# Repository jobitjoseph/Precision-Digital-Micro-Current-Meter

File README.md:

# Precision-Digital-Micro-Current-Meter

Keeping track of extremely low current levels is often essential when developing or testing low-power devices, especially in the field of embedded systems and battery-operated electronics. This project presents a compact and reliable micro current meter that makes such measurements straightforward and accessible. It is built around an STM32 microcontroller and features an OLED display for real-time readouts. The analog front end is designed to detect small current flows accurately, converting them into voltage levels that the microcontroller can process with high resolution. Whether you're measuring sleep current in a sensor node or characterising a power-efficient circuit, the device offers a clear and immediate view of power consumption trends.

The meter is designed for ease of use on the workbench, with a focus on readability, stability, and portability. The OLED display provides a crisp output that remains visible under most lighting conditions, while the microcontroller handles signal processing and automatic range detection. Calibration routines ensure measurement consistency across various load conditions. With no need for external tools or complex setups, the device offers a plug-and-play experience for engineers, developers, or hobbyists working with ultra-low power electronics. Its practical design makes it a useful tool for anyone seeking to analyse power usage with precision and simplicity.

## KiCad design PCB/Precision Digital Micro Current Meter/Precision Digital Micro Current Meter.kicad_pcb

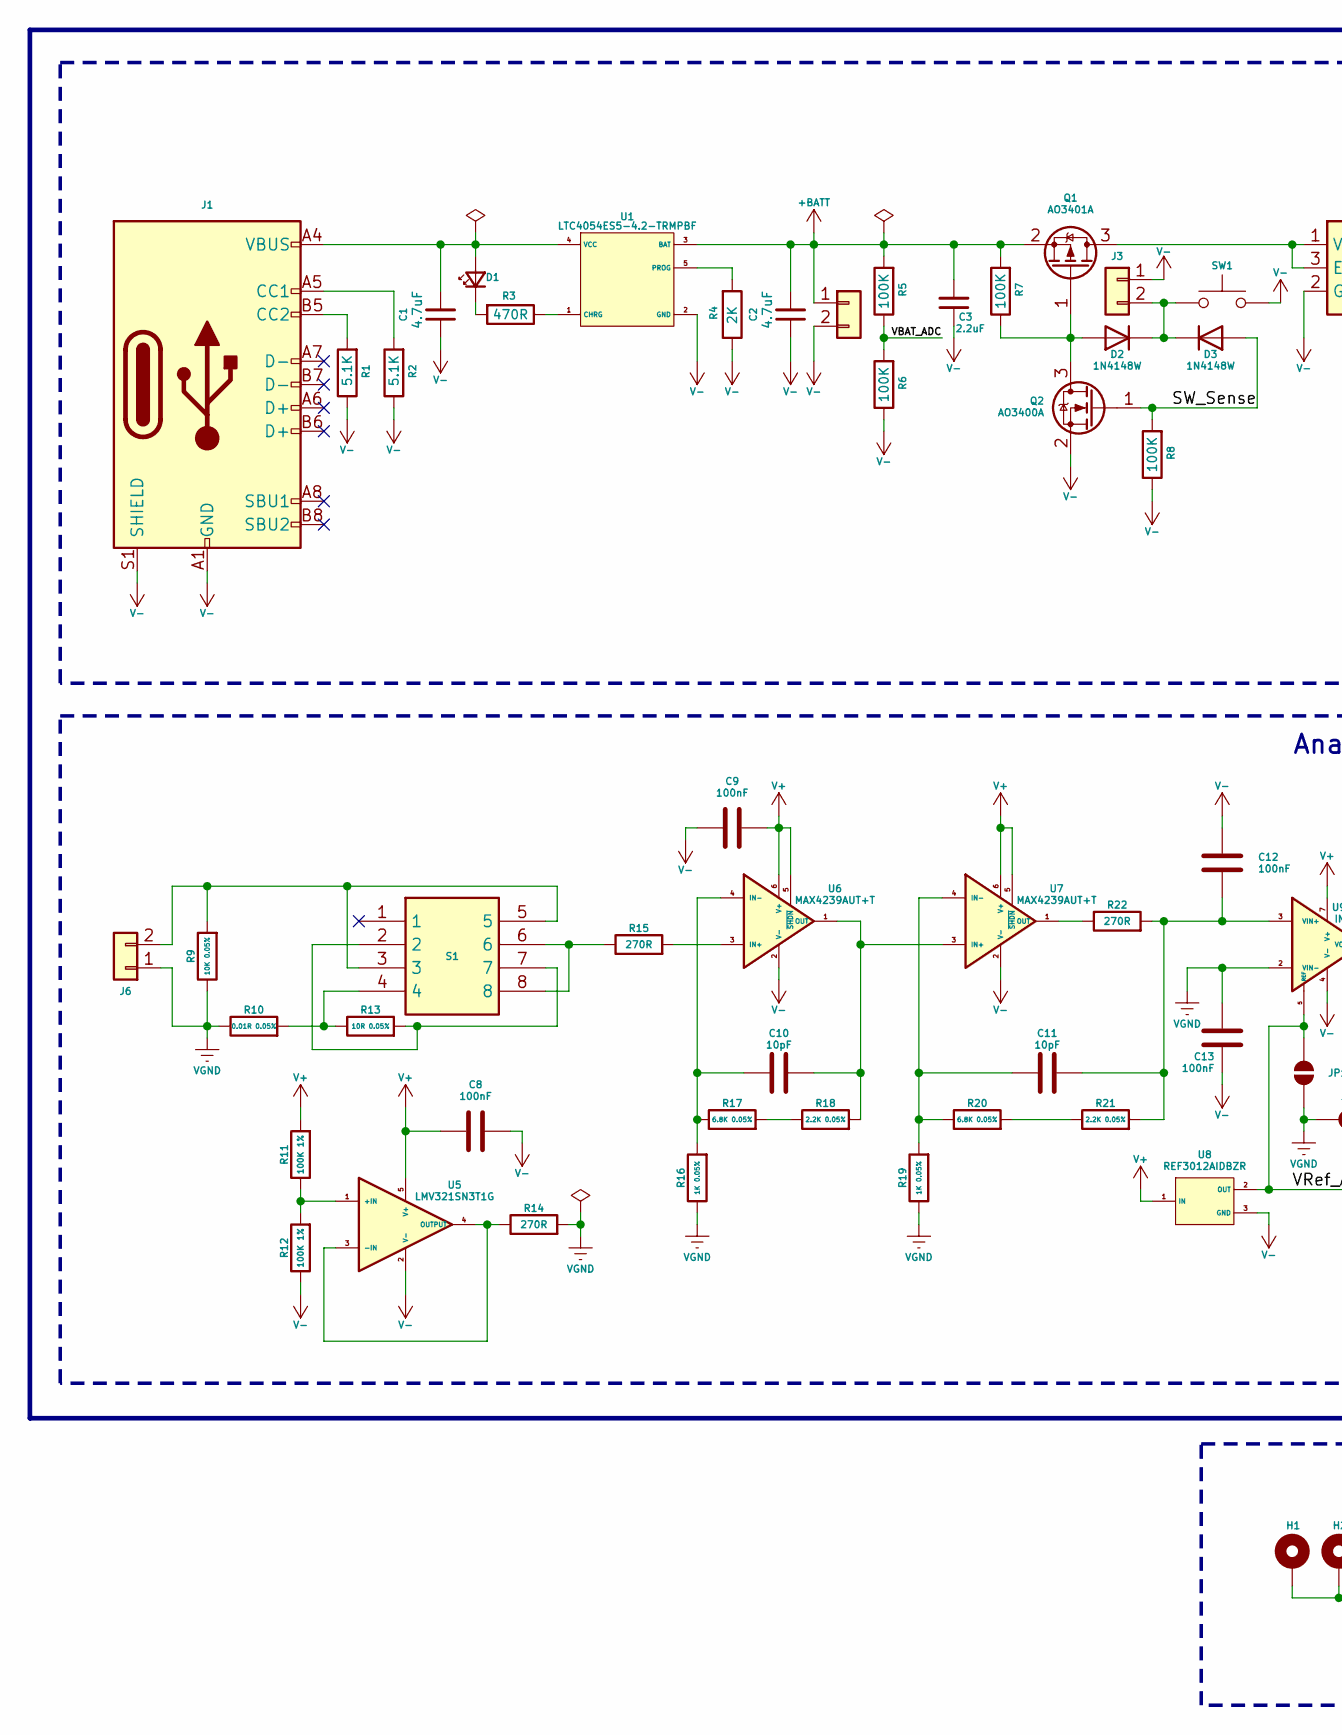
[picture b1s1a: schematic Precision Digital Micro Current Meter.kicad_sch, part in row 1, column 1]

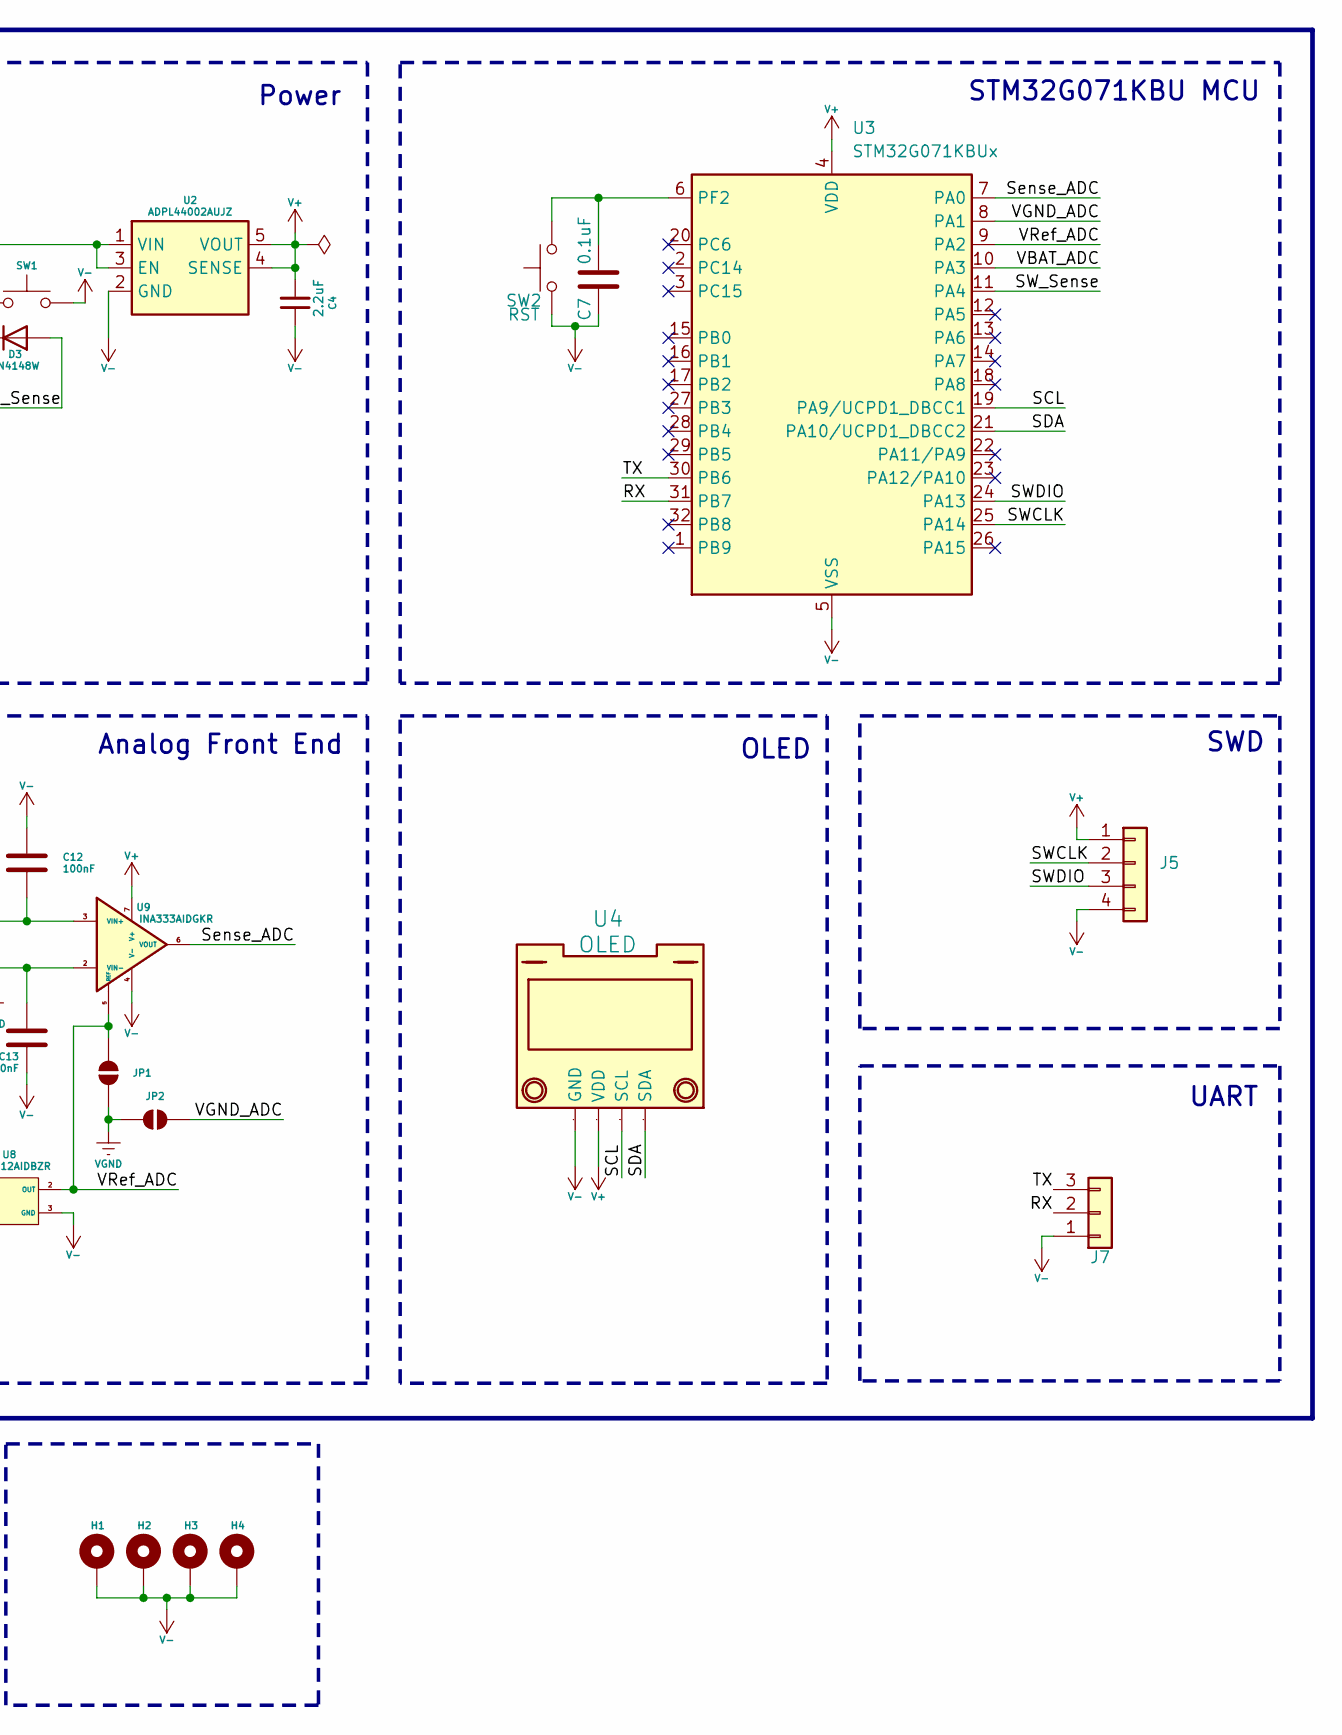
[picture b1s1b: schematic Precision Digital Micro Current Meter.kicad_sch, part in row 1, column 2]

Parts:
C1, C2: 4.7uF; C_0603_1608Metric
C3, C4: 2.2uF; C_0603_1608Metric
C7: 0.1uF; C_0603_1608Metric
C8, C9, C12, C13: 100nF; C_0603_1608Metric
C10, C11: 10pF; C_0603_1608Metric
D1: LED_Small; LED_0603_1608Metric
D2, D3: 1N4148W; D_SOD-123
H1, H2, H3, H4: MountingHole_Pad; MountingHole_2.5mm_Pad
J1: USB_C_Receptacle_USB2.0_16P; USB_C_Receptacle_Palconn_UTC16-G
J2: B2B-PH-SM4-TB(LF)(SN); JST_PH_B2B-PH-K_1x02_P2.00mm_Vertical; DigiKey Part Number 455-1704-ND
J3: Conn_01x02; JST_PH_B2B-PH-K_1x02_P2.00mm_Vertical
J5: Conn_01x04; PinHeader_1x04_P2.54mm_Vertical
J6: Conn_01x02; Banana_Jack_2Pin
J7: Conn_01x03; PinHeader_1x03_P2.54mm_Vertical
JP1, JP2: SolderJumper_2_Open; SolderJumper-2_P1.3mm_Open_TrianglePad1.0x1.5mm
Q1: AO3401A; SOT-23
Q2: AO3400A; SOT-23
R1, R2: 5.1K; R_0603_1608Metric
R3: 470R; R_0603_1608Metric
R4: 2K; R_0603_1608Metric
R5, R6, R7, R8: 100K; R_0603_1608Metric
R9: 10K 0.05%; R_0805_2012Metric
R10: 0.01R 0.05%; R_2512_6332Metric
R11, R12: 100K 1%; R_0603_1608Metric
R13: 10R 0.05%; R_0805_2012Metric
R14, R15, R22: 270R; R_0603_1608Metric
R16, R19: 1K 0.05%; R_0603_1608Metric
R17, R20: 6.8K 0.05%; R_0603_1608Metric
R18, R21: 2.2K 0.05%; R_0603_1608Metric
S1: L203011MS02Q; L203111MS02Q; Mouser Part Number 611-L203011MS02Q
SW1: SW_Push; SW_PUSH_6mm
SW2: RST; Tactile 3x4x2mm TS-A010
U1: LTC4054ES5-4.2-TRMPBF; S_5_ADI
U2: ADPL44002AUJZ; SOT95P280X100-5N; Manufacturer_Part_Number ADPL44002AUJZ2.5-R7
U3: STM32G071KBUx; QFN-32-1EP_5x5mm_P0.5mm_EP3.45x3.45mm
U4: OLED; MODULE_DM-OLED096-636
U5: LMV321SN3T1G; SOT95P275X110-5N; Mouser Part Number 863-LMV321SN3T1G
U6, U7: MAX4239AUT+T; SOT95P280X145-6N; Mouser Part Number 700-MAX4239AUT+T
U8: REF3012AIDBZR; DBZ3
U9: INA333AIDGKR; SOP65P490X110-8N

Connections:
+BATT: C2.2, C3.2, J2.1, Q1.2 (S), R5.2, R7.2, U1.3 (BAT)
/RX: J7.2, U3.31 (PB7); also elsewhere on the board
/SCL: U3.19 (PA9/UCPD1_DBCC1), U4.3 (SCL)
/SDA: U3.21 (PA10/UCPD1_DBCC2), U4.4 (SDA)
/SWCLK: J5.2, U3.25 (PA14)
/SWDIO: J5.3, U3.24 (PA13)
/SW_Sense: D3.2 (A), Q2.1 (G), R8.2, U3.11 (PA4)
/Sense_ADC: U3.7 (PA0), U9.6 (VOUT)
/TX: J7.3, U3.30 (PB6); also elsewhere on the board
/VBAT_ADC: R5.1, R6.2, U3.10 (PA3)
/VGND_ADC: JP2.1 (A), U3.8 (PA1)
/VRef_ADC: JP1.2 (B), U3.9 (PA2), U8.2 (OUT), U9.5 (REF)
unnamed: C1.2, D1.2 (A), J1.A4 (VBUS), J1.A9 (VBUS), J1.B4 (VBUS), J1.B9 (VBUS), U1.4 (VCC)
unnamed: D1.1 (K), R3.2
unnamed: D2.2 (A), Q1.1 (G), Q2.3 (D), R7.1
unnamed: D2.1 (K), D3.1 (K), J3.2, SW1.1
unnamed: J1.A5 (CC1), R2.2
unnamed: J1.B5 (CC2), R1.2
unnamed: J6.2, R9.2, S1.3, S1.5
unnamed: Q1.3 (D), U2.1 (VIN), U2.3 (EN)
unnamed: R10.2, R13.1, S1.4
unnamed: R13.2, S1.2, S1.7
unnamed: R15.1, S1.6, S1.8
unnamed: R17.2, R18.1
unnamed: R20.2, R21.1
unnamed: R3.1, U1.1 (CHRG)
unnamed: R4.2, U1.5 (PROG)
unnamed: C7.2, SW2.2, U3.6 (PF2)
unnamed: R11.1, R12.2, U5.1 (+IN)
unnamed: R14.1, U5.3 (-IN), U5.4 (OUTPUT)
unnamed: R15.2, U6.3 (IN+)
unnamed: C10.1, R16.2, R17.1, U6.4 (IN-)
unnamed: C10.2, R18.2, U6.1 (OUT), U7.3 (IN+)
unnamed: C11.1, R19.2, R20.1, U7.4 (IN-)
unnamed: R22.1, U7.1 (OUT)
unnamed: C11.2, C12.1, R21.2, R22.2, U9.3 (VIN+)
V+: C4.2, C8.1, C9.2, J5.1, R11.2, U2.4 (SENSE), U2.5 (VOUT), U3.4 (VDD), U4.2 (VDD), U5.5 (V+), U6.5 (~SHDN), U6.6 (V+), U7.5 (~SHDN), U7.6 (V+), U8.1 (IN), U9.7 (V+)
V-: C1.1, C2.1, C3.1, C4.1, C7.1, C8.2, C9.1, C12.2, C13.1, H1.1, H2.1, H3.1, H4.1, J1.A1 (GND), J1.A12 (GND), J1.B1 (GND), J1.B12 (GND), J1.S1 (SHIELD), J2.2, J3.1, J5.4, J7.1, Q2.2 (S), R1.1, R2.1, R4.1, R6.1, R8.1, R12.1, SW1.2, SW2.1, U1.2 (GND), U2.2 (GND), U3.5 (VSS), U3.33 (VSS), U4.1 (GND), U5.2 (V-), U6.2 (V-), U7.2 (V-), U8.3 (GND), U9.4 (V-); also elsewhere on the board
VGND: C13.2, J6.1, JP1.1 (A), JP2.2 (B), R9.1, R10.1, R14.2, R16.1, R19.1, U9.2 (VIN-)

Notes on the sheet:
Power
STM32G071KBU MCU
OLED
UART
SWD
Analog Front End

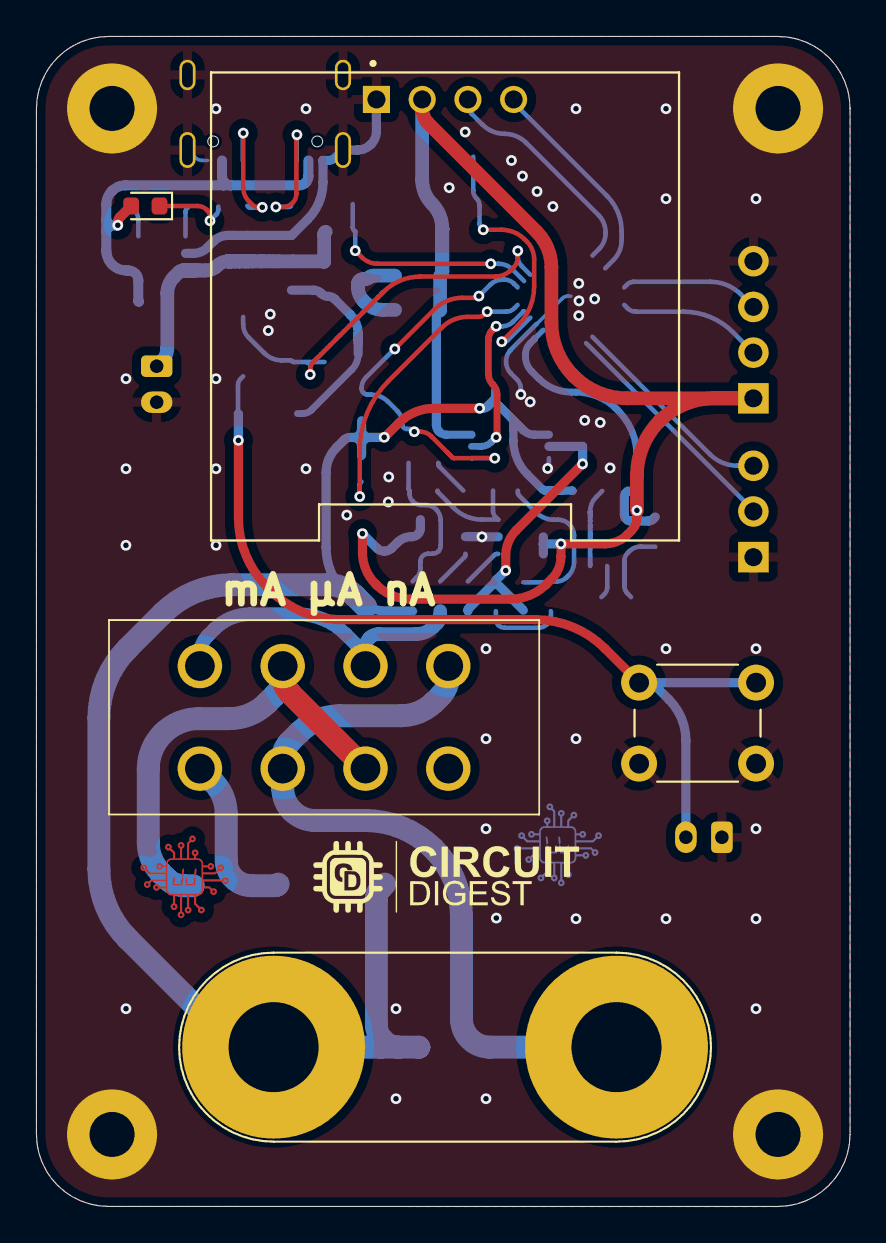
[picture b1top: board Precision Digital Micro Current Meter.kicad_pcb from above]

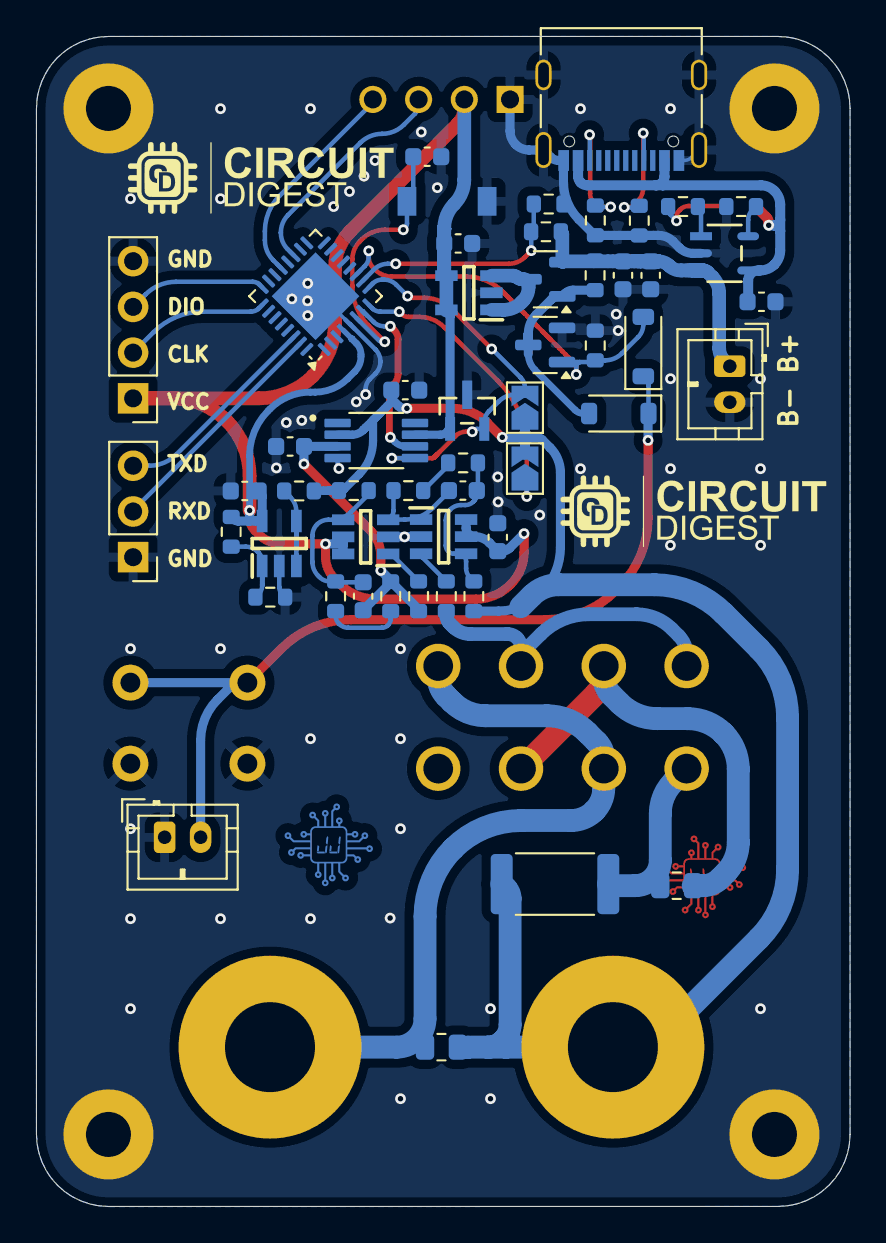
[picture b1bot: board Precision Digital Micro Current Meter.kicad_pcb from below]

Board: 2 copper layers, 45.2 x 65.0 mm, 62 parts (53 on the bottom side), 39 nets.

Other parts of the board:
J4: Conn_01x03; PinHeader_1x03_P2.54mm_Vertical

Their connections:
/RX: J4.2; also elsewhere on the board
/TX: J4.3; also elsewhere on the board
V-: J4.1; also elsewhere on the board

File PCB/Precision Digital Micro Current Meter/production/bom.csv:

Designator,Footprint,Quantity,Value,LCSC Part #
"C1, C2",0603,2,4.7uF,
"C10, C11",0603,2,10pF,
"C12, C13, C8, C9",0603,4,100nF,
"C3, C4",0603,2,2.2uF,
C7,0603,1,0.1uF,
D1,0603,1,LED_Small,
"D2, D3",D_SOD-123,2,1N4148W,
J1,USB_C_Receptacle_Palconn_UTC16-G,1,USB_C_Receptacle_USB2.0_16P,
J2,JST_PH_B2B-PH-K_1x02_P2.00mm_Vertical,1,B2B-PH-SM4-TB(LF)(SN),
J3,JST_PH_B2B-PH-K_1x02_P2.00mm_Vertical,1,Conn_01x02,
J4,PinHeader_1x03_P2.54mm_Vertical,1,Conn_01x03,
J5,PinHeader_1x04_P2.54mm_Vertical,1,Conn_01x04,
J6,Banana_Jack_2Pin,1,Conn_01x02,
"JP1, JP2",SolderJumper-2_P1.3mm_Open_TrianglePad1.0x1.5mm,2,SolderJumper_2_Open,
Q1,SOT-23,1,AO3401A,
Q2,SOT-23,1,AO3400A,
"R1, R2",0603,2,5.1K,
R10,2512,1,0.01R 0.05%,
"R11, R12",0603,2,100K 1%,
R13,0805,1,10R 0.05%,
"R14, R15, R22",0603,3,270R,
"R16, R19",0603,2,1K 0.05%,
"R17, R20",0603,2,6.8K 0.05%,
"R18, R21",0603,2,2.2K 0.05%,
R3,0603,1,470R,
R4,0603,1,2K,
"R5, R6, R7, R8",0603,4,100K,
R9,0805,1,10K 0.05%,
S1,L203111MS02Q,1,L203011MS02Q,
SW1,SW_PUSH_6mm,1,SW_Push,
SW2,Tactile 3x4x2mm TS-A010,1,RST,
U1,S_5_ADI,1,LTC4054ES5-4.2-TRMPBF,
U2,SOT95P280X100-5N,1,ADPL44002AUJZ,
U3,QFN-32-1EP_5x5mm_P0.5mm_EP3.45x3.45mm,1,STM32G071KBUx,
U4,MODULE_DM-OLED096-636,1,OLED,
U5,SOT95P275X110-5N,1,LMV321SN3T1G,
"U6, U7",SOT95P280X145-6N,2,MAX4239AUT+T,
U8,DBZ3,1,REF3012AIDBZR,
U9,SOP65P490X110-8N,1,INA333AIDGKR,

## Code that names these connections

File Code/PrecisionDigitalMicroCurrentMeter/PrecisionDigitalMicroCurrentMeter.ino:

/*
 * Project Name: Precision Digital Micro Current Meter
 * Project Brief: Precision Digital Micro Current Meter based STM32G071KBU MCU.
 * Author: Jobit Joseph @ https://github.com/jobitjoseph
 * IDE: Arduino IDE 2.3.6
 * Arduino Core: ESP32 Arduino Core V 3.2.0
 * Dependencies : U8g2 Library V 2.35.30 @ https://github.com/olikraus/u8g2
 *
 * Copyright © Jobit Joseph
 * Copyright © Semicon Media Pvt Ltd
 * Copyright © Circuitdigest.com
 * 
 * This code is licensed under the following conditions:
 *
 * 1. Non-Commercial Use:
 * This program is free software: you can redistribute it and/or modify it
 * for personal or educational purposes under the condition that credit is given 
 * to the original author. Attribution is required, and the original author 
 * must be credited in any derivative works or distributions.
 *
 * 2. Commercial Use:
 * For any commercial use of this software, you must obtain a separate license
 * from the original author. Contact the author for permissions or licensing
 * options before using this software for commercial purposes.
 *
 * THE SOFTWARE IS PROVIDED "AS IS", WITHOUT WARRANTY OF ANY KIND, EXPRESS OR
 * IMPLIED, INCLUDING BUT NOT LIMITED TO THE WARRANTIES OF MERCHANTABILITY, 
 * FITNESS FOR A PARTICULAR PURPOSE, AND NONINFRINGEMENT. IN NO EVENT SHALL 
 * THE AUTHORS OR COPYRIGHT HOLDERS BE LIABLE FOR ANY CLAIM, DAMAGES, OR OTHER 
 * LIABILITY, WHETHER IN AN ACTION OF CONTRACT, TORT, OR OTHERWISE, ARISING 
 * FROM, OUT OF, OR IN CONNECTION WITH THE SOFTWARE OR THE USE OR OTHER 
 * DEALINGS IN THE SOFTWARE.
 *
 * Author: Jobit Joseph
 * Date: 23 May 2025
 *
 * For commercial use or licensing requests, please contact [jobitjoseph1@gmail.com].
 */

#include <Wire.h>
#include <HardwareSerial.h>
#include <U8g2lib.h>
#define LATCH_PIN PA4
#define NUM_SAMPLES 2
#define SAMPLE_DELAY 10
#define REF_VOLTAGE 1249.3f  // float for precision

// Define our custom HardwareSerial
HardwareSerial MySerial(PB6, PB7);  // TX, RX
U8G2_SSD1306_128X64_NONAME_F_HW_I2C u8g2(U8G2_R0, /* reset=*/U8X8_PIN_NONE);
volatile bool buttonPressed = false;
volatile bool buttonReleased = false;
volatile unsigned long lastInterruptTime = 0;
unsigned long releaseTime = 0;
const unsigned long debounceDelay = 50;
const unsigned long shutdownDelay = 1000;

unsigned long lastBatteryUpdate = 0;
float batteryVoltage = 0;
int AmpV = 0;
float AmpVF = 0;
int batteryPercent = 0;

void buttonISR() {
  unsigned long now = millis();
  if (now - lastInterruptTime < debounceDelay) return;

  if (digitalRead(LATCH_PIN) == LOW) {
    buttonPressed = true;
    buttonReleased = false;
  } else {
    if (buttonPressed) {
      buttonReleased = true;
      releaseTime = now;
      delay(500);
      pinMode(LATCH_PIN, OUTPUT);
      digitalWrite(LATCH_PIN, LOW);
      while (1)
        ;
    }
    buttonPressed = false;
  }
  lastInterruptTime = now;
}

void setup() {
  pinMode(LATCH_PIN, INPUT_PULLUP);
  attachInterrupt(digitalPinToInterrupt(LATCH_PIN), buttonISR, CHANGE);
  MySerial.begin(115200);
  MySerial.println("STM32G071 ADC with External Reference (PA2)");
  analogReadResolution(12);
  u8g2.begin();
}

void loop() {
  unsigned long now = millis();
  if (now - lastBatteryUpdate > 500) {
    float vdda = measureVDDA();
    batteryVoltage = measureInputVoltage(PA3, vdda) * 2.0f;
    float Vref = measureInputVoltage(PA1, vdda);
    float ampVoltage = measureInputVoltage(PA0, vdda);
    //AmpV = ((int)((ampVoltage - Vref) / 2.0f)) - 3;
    //float error_percent = 4.77f;
    //AmpV = (int)(((ampVoltage - Vref) / 2.0f) * (1.0f - error_percent / 100.0f))-3;
    float raw = ((ampVoltage - Vref) / 1.0f);
    float offset = 6.0f;
    float error_percent = 0.0f;
    //AmpV = (int)((raw - offset) * (1.0f - error_percent / 100.0f));
    AmpVF = (raw  * (1.0f - error_percent / 100.0f)- offset);
    AmpV = (int)AmpVF;
    batteryPercent = batteryLevelPercent((int)batteryVoltage);

    MySerial.print("VDDA: "); MySerial.print(vdda);
    MySerial.print(" mV, Vref: "); MySerial.print(Vref);
    MySerial.print(" mV, PA2: "); MySerial.print(measureInputVoltage(PA2, vdda));
    MySerial.print(" mV, Amp: "); MySerial.println(AmpV);

    lastBatteryUpdate = now;

    u8g2.clearBuffer();
    u8g2.setFont(u8g2_font_5x8_tr);

    int iconX = 96, iconY = 0, iconW = 28, iconH = 12;
    char batteryPercentStr[6];
    itoa(batteryPercent, batteryPercentStr, 10);
    strcat(batteryPercentStr, "%");
    u8g2.drawStr(iconX - 20, iconY + 10, batteryPercentStr);

    drawBatteryIconWithBars(iconX, iconY, iconW, iconH, batteryPercent);

    char AmpStr[7];
    if (AmpV < 0) {
      sprintf(AmpStr, "-%04d", abs(AmpV));
    } else {
      sprintf(AmpStr, " %04d", AmpV);
    }

    u8g2.setFont(u8g2_font_inb33_mn);
    u8g2.drawStr(-10, 62, AmpStr);
    u8g2.sendBuffer();
  }
}

float measureVDDA() {

  uint32_t sum = 0;
  for (int i = 0; i < NUM_SAMPLES; i++) {
    sum += oversampledADC(PA1);
    delayMicroseconds(SAMPLE_DELAY);
  }
  float adcAvg = (float)sum / NUM_SAMPLES;
  float vdda = (REF_VOLTAGE * 65535.0f) / adcAvg;
  return vdda;
}

float measureInputVoltage(uint32_t pin, float vdda) {
  uint32_t sum = 0;
  for (int i = 0; i < NUM_SAMPLES; i++) {
    sum += oversampledADC(pin);  
    delayMicroseconds(SAMPLE_DELAY);
  }
  float adcAvg = (float)sum / NUM_SAMPLES;
  float voltage = (adcAvg * vdda) / 65535.0f;
  return voltage;
}

uint32_t oversampledADC(uint32_t pin) {
  uint32_t sum = 0;
  const int oversample_count = 256;  // 2^(2 × (16 - 12)) = 256

  for (int i = 0; i < oversample_count; i++) {
    sum += analogRead(pin);  // 12-bit reading
    delayMicroseconds(SAMPLE_DELAY);   // optional: allow settling
  }

  // Average and scale to 16-bit range
  uint32_t avg = sum / oversample_count;
  uint32_t adc16 = avg << 4;  // 12-bit to 16-bit shift (multiply by 16)
  // Ignore 3 LSBs
  const int ignore_lsb = 4;
  adc16 = (adc16 >> ignore_lsb) << ignore_lsb;

  return adc16;
}

int batteryLevelPercent(int v_bat) {
  int percent = (v_bat - 3000) * 100 / (4200 - 3000);
  if (percent > 100) percent = 100;
  if (percent < 0) percent = 0;
  return percent;
}

void drawBatteryIconWithBars(int x, int y, int w, int h, int percent) {
  u8g2.drawFrame(x, y, w, h);
  u8g2.drawBox(x + w, y + h / 3, 2, h / 3);

  int numBars = 4;
  int barSpacing = 2;
  int barWidth = (w - 6 - (numBars - 1) * barSpacing) / numBars;
  int barHeight = h - 4;
  int barsToDraw = (percent + 24) / 25;

  for (int i = 0; i < barsToDraw; i++) {
    int bx = x + 2 + i * (barWidth + barSpacing);
    u8g2.drawBox(bx, y + 2, barWidth, barHeight);
  }
}
